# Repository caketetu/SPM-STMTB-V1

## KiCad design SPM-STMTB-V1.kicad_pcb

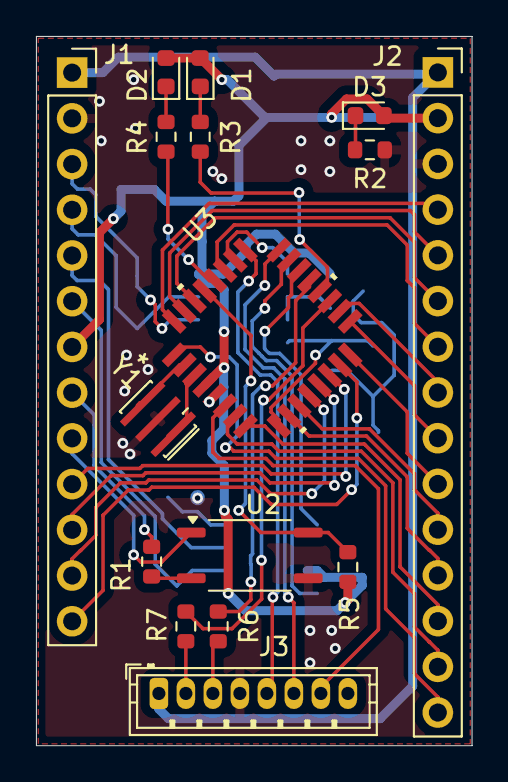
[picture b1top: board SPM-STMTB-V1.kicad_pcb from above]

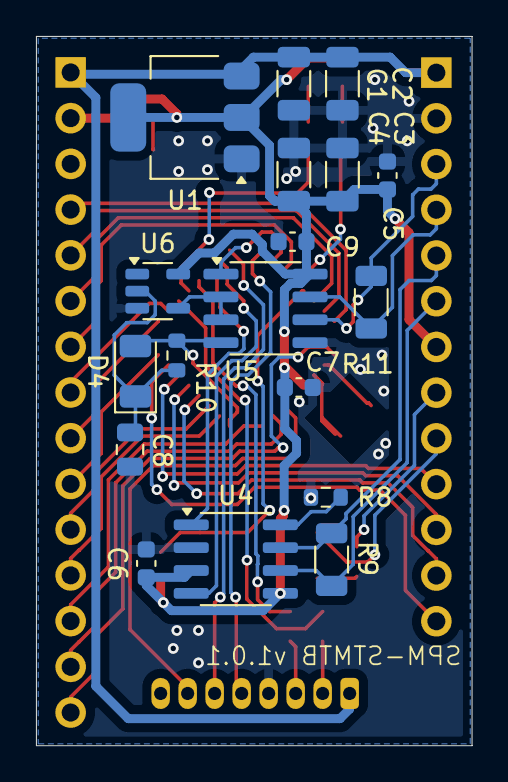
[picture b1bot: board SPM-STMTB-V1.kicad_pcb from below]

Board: 2 copper layers, 24.2 x 39.4 mm, 34 parts (18 on the bottom side), 48 nets.

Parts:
C1, C2, C3, C4: C10u; C_1206_3216Metric
C5, C6, C7, C9: C0.1u; C_0603_1608Metric
C8: C0.01u; C_0805_2012Metric
D1, D2, D3: LED; LED_0603_1608Metric
D4: D; D_1206_3216Metric
J1: Conn_01x13_Pin; PinSocket_1x13_P2.54mm_Vertical
J2: Conn_01x15_Pin; PinSocket_1x15_P2.54mm_Vertical
J3: Conn_01x08_Pin; JST_ZH_B8B-ZR_1x08_P1.50mm_Vertical
R1: R4.7k; R_0603_1608Metric
R2, R3, R4: R1K; R_0603_1608Metric
R5, R6, R7: R1k; R_0603_1608Metric
R8: R150; R_0603_1608Metric
R9: R150; R_1206_3216Metric
R10: R10k; R_0603_1608Metric
R11: R120; R_1206_3216Metric
U1: LD1117S33TR_SOT223; SOT-223-3_TabPin2
U2: TLP185; SOIC-4_4.55x3.7mm_P2.54mm
U3: STM32C092KBT6; LQFP-32_STM
U4: MCP2562-E-SN; SOIC-8_3.9x4.9mm_P1.27mm
U5: MAX3485; SOIC-8_3.9x4.9mm_P1.27mm
U6: 74LVC1G14; SOT-23-5
Y1: Resonator; Resonator_SMD_Murata_CSTxExxV-3Pin_3.0x1.1mm_HandSoldering

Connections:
+3V3: C3.1, C4.1, C5.1, C6.1, C7.1, C9.1, D1.2 (A), D2.2 (A), D3.2 (A), J1.7, J2.2, R5.1, U1.2 (VO), U3.4 (VDD/VDDA), U4.3 (VDD), U4.5 (Vio), U5.8 (VCC), U6.5 (VCC)
+5V: C1.1, C2.1, J1.1, J2.1, J3.1, U1.3 (VI)
CANH: J1.5, R9.1, U4.7 (CANH)
CANL: J1.6, R9.2, U4.6 (CANL)
EN_SIG: J1.9, U2.1
GND: C1.2, C2.2, C3.2, C4.2, C5.2, C6.2, C7.2, C8.2, C9.2, J1.2, J2.3, J3.4, R2.1, R8.1, U1.1 (GND), U2.4, U3.5 (VSS/VSSA), U4.2 (VSS), U5.5 (GND), U6.3 (GND), Y1.2
GND1: J1.8, R1.2
I2C_SCL: J2.6, U3.30 (PB6)
I2C_SDA: J2.5, U3.31 (PB7)
IO0: J2.10, U3.16 (PB1)
IO1: J2.7, U3.27 (PB3)
NRST: J3.7, U3.6 (PF2-NRST)
unnamed: D1.1 (K), R3.2
unnamed: D2.1 (K), R4.2
unnamed: D3.1 (K), R2.2
unnamed: C8.1, D4.1 (K), R10.2, U6.2
unnamed: R1.1, U2.3
unnamed: R6.1, U3.19 (PA9)
unnamed: R7.2, U3.21 (PA10)
unnamed: U3.2 (PC14-OSCX_IN), Y1.3
unnamed: U3.3 (PC15-OSCX_OUT), Y1.1
unnamed: R8.2, U4.8 (STBY)
RE_DE: U5.2 (~RE), U5.3 (DE), U6.4
RS485+: J1.3, R11.1, U5.6 (A)
RS485-: J1.4, R11.2, U5.7 (B)
RX3_RX: J2.15, U3.1 (PB9)
RX3_TX: J2.9, U3.17 (PB2)
RX4_RX: J2.13, U3.8 (PA1)
RX4_TX: J2.14, U3.7 (PA0)
SPI_CLK: J2.4, U3.32 (PB8)
SPI_MISO: J2.12, U3.10 (PA3)
SPI_MOSI: J2.11, U3.11 (PA4)
SPI_SS: J2.8, U3.18 (PA8)
SYS-LED1: R3.1, U3.20 (PC6)
SYS-LED2: R4.1, U3.28 (PB4)
SYS_CAN-RX: U3.23 (PA12[PA10]), U4.4 (RXD)
SYS_CAN-TX: U3.22 (PA11[PA9]), U4.1 (TXD)
SYS_EN: R5.2, U2.6, U3.29 (PB5)
SYS_JTCK-SWCLK: J3.5, U3.25 (PA14-BOOT0)
SYS_JTCK-SWDIO: J3.6, U3.24 (PA13)
SYS_RX: J3.3, R7.1
SYS_RX2: U3.26 (PA15), U5.1 (RO)
SYS_SPI-CLK: J1.12, U3.12 (PA5)
SYS_SPI-MISO: J1.11, U3.13 (PA6)
SYS_SPI-MOSI: J1.10, U3.14 (PA7)
SYS_SPI-SS: J1.13, U3.15 (PB0)
SYS_TX: J3.2, R6.2
SYS_TX2: D4.2 (A), R10.1, U3.9 (PA2), U5.4 (DI)
